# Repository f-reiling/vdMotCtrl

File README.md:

# vdMotCtrl
Controls up to 6 HmIP-VDMOT drives via I2C or UART interface. 

PCB uses ATmega168P as controller with L9110s as drivers. External interfaces are I2C and UART. Socket for ESP12 is also availble for wireless connection. 2 PCBs can be stacked, communication is planned via I2C then.

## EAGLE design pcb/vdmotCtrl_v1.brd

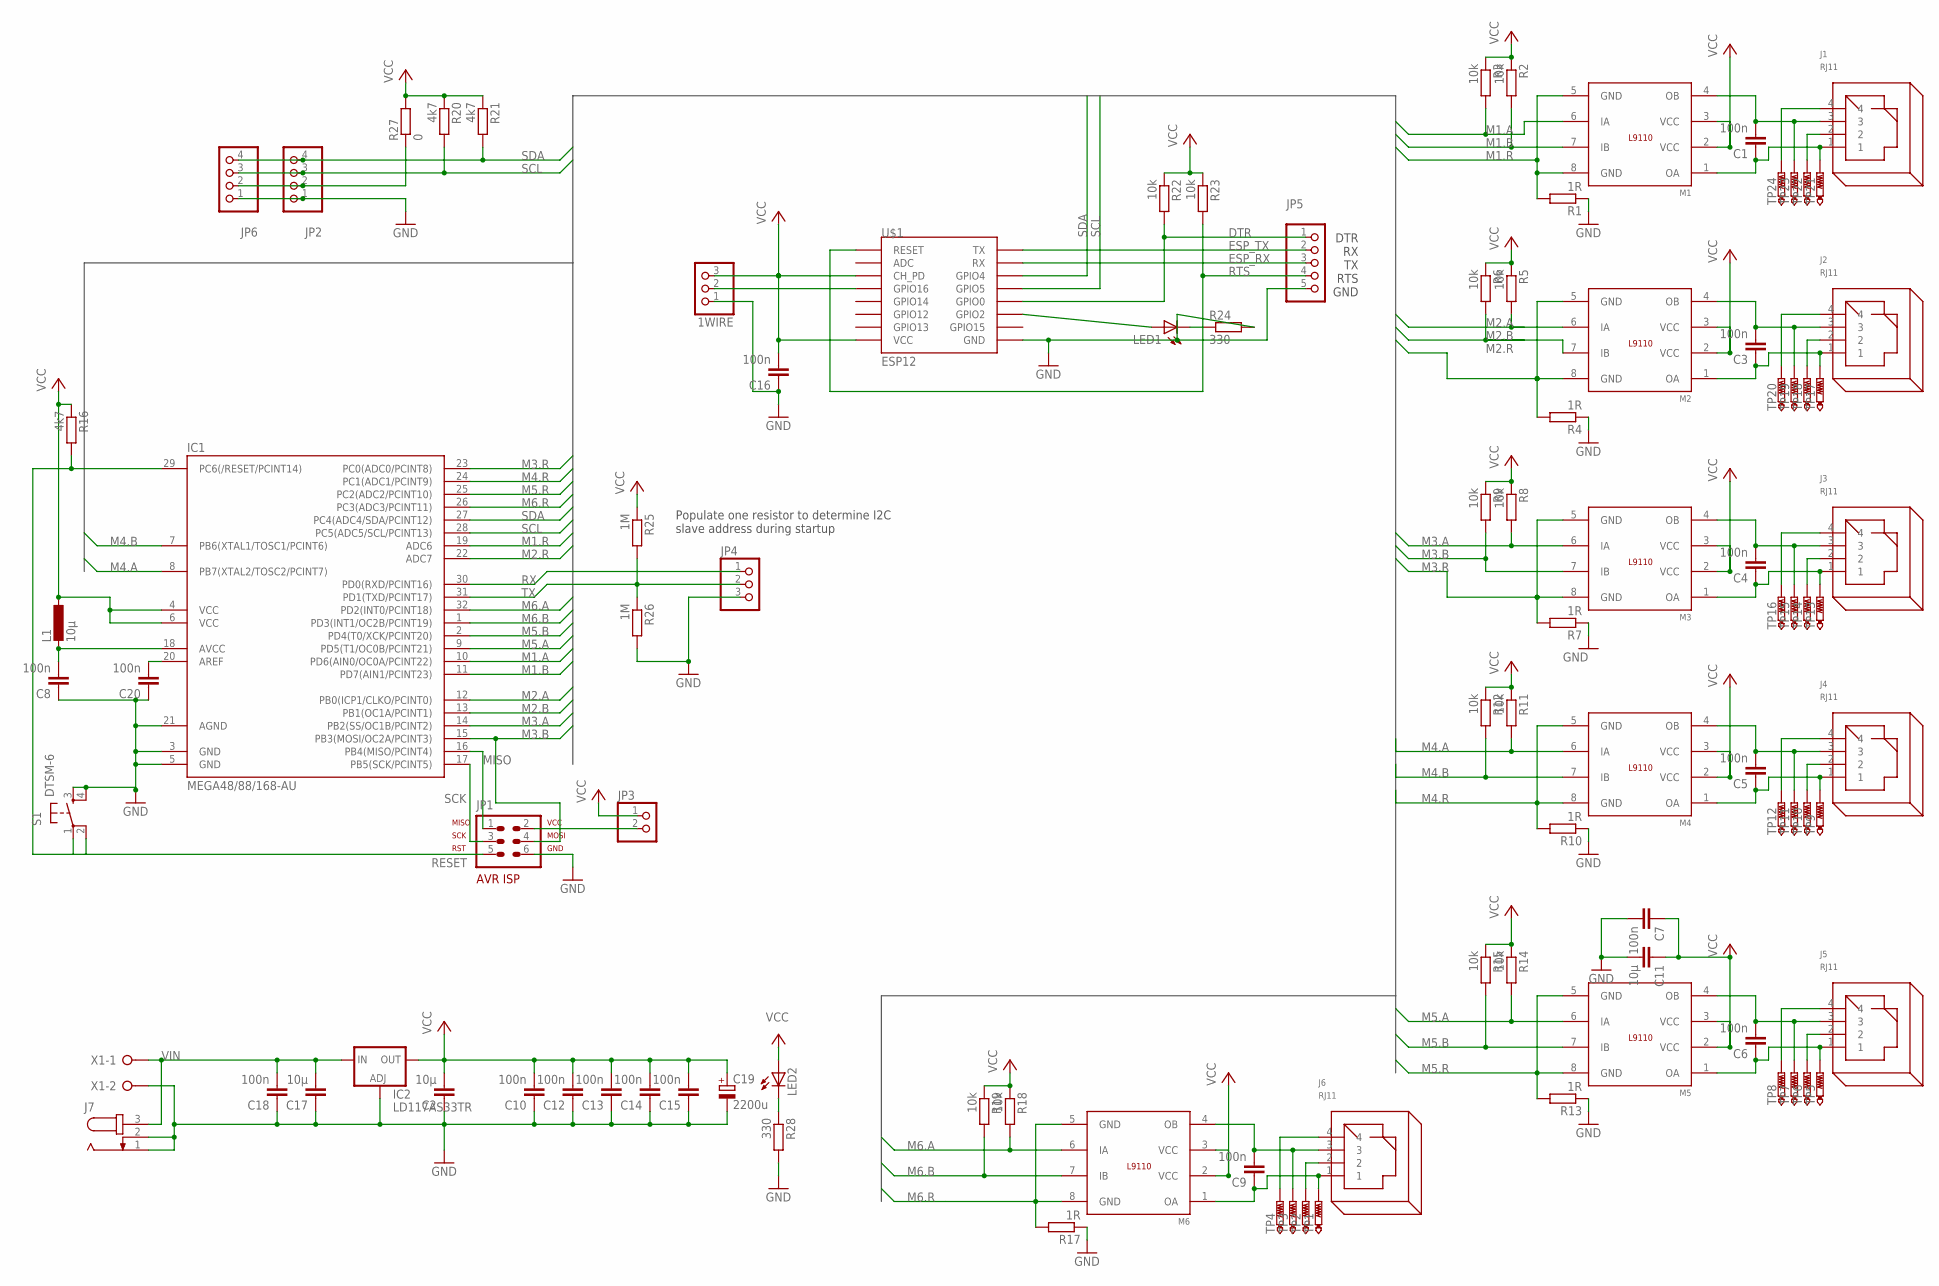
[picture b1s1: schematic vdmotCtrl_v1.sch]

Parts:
1WIRE: PINHD-1X3; 1X03
C1, C3, C4, C5, C6, C7, C8, C9, C10, C12, C13, C14, C15, C16, C18, C20: 100n; C0805
C2, C11, C17: 10µ; C0805
C19: 2200u; E5-10,5
IC1: MEGA48/88/168-AU; TQFP32-08
IC2: LD117AS33TR; SOT223
J1, J2, J3, J4, J5, J6: RJ11
J7: JACK-PLUG0; SPC4077
JP1: AVR-ISP-6VERT; AVR-ISP-6
JP2, JP6: PINHD-1X4; 1X04
JP3: PINHD-1X2; 1X02
JP4: PINHD-1X3; 1X03
JP5: PINHD-1X5; 1X05
L1: 10µ; 0204/7
LED1, LED2: RED; SML0805
M1, M2, M3, M4, M5, M6: L9110; SO8P
R1, R4, R7, R10, R13, R17: 1R; R0805
R2, R3, R5, R6, R8, R9, R11, R12, R14, R15, R18, R19, R22, R23: 10k; R0805
R16, R20, R21: 4k7; R0805
R24, R28: 330; R0805
R25, R26: 1M; R0805
R27: 0; M0805
S1: DTSM-6
TP1, TP2, TP3, TP4, TP5, TP6, TP7, TP8, TP9, TP10, TP11, TP12, TP13, TP14, TP15, TP16, TP17, TP18, TP19, TP20, TP21, TP22, TP23, TP24: PTR1TP15SQ; TP15SQ
U$1: ESP12
X1: W237-02P; W237-132

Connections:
DTR: JP5.1, R22.2, U$1.GPIO0
ESP_RX: JP5.3, U$1.RX
ESP_TX: JP5.2, U$1.TX
GND: 1WIRE.1, C2.1, C7.2, C8.1, C10.1, C11.2, C12.1, C13.1, C14.1, C15.1, C16.1, C17.1, C18.1, C19.-, C20.1, IC1.3 (GND), IC1.5 (GND), IC1.21 (AGND), IC2.1 (ADJ), J7.1, J7.2, JP1.6, JP2.1, JP4.3, JP5.5, JP6.1, R1.1, R4.1, R7.1, R10.1, R13.1, R17.1, R24.2, R26.2, R28.2, S1.3, S1.4, U$1.GND, X1.2
M1.A: IC1.10 (PD6(AIN0/OC0A/PCINT22)), M1.6 (IA), R3.2
M1.B: IC1.11 (PD7(AIN1/PCINT23)), M1.7 (IB), R2.2
M1.R: IC1.19 (ADC6), M1.5 (GND), M1.8 (GND), R1.2
M2.A: IC1.12 (PB0(ICP1/CLKO/PCINT0)), M2.6 (IA), R5.2
M2.B: IC1.13 (PB1(OC1A/PCINT1)), M2.7 (IB), R6.2
M2.R: IC1.22 (ADC7), M2.5 (GND), M2.8 (GND), R4.2
M3.A: IC1.14 (PB2(SS/OC1B/PCINT2)), M3.6 (IA), R8.2
M3.B: IC1.15 (PB3(MOSI/OC2A/PCINT3)), JP1.4, M3.7 (IB), R9.2
M3.R: IC1.23 (PC0(ADC0/PCINT8)), M3.5 (GND), M3.8 (GND), R7.2
M4.A: IC1.8 (PB7(XTAL2/TOSC2/PCINT7)), M4.6 (IA), R11.2
M4.B: IC1.7 (PB6(XTAL1/TOSC1/PCINT6)), M4.7 (IB), R12.2
M4.R: IC1.24 (PC1(ADC1/PCINT9)), M4.5 (GND), M4.8 (GND), R10.2
M5.A: IC1.9 (PD5(T1/OC0B/PCINT21)), M5.6 (IA), R14.2
M5.B: IC1.2 (PD4(T0/XCK/PCINT20)), M5.7 (IB), R15.2
M5.R: IC1.25 (PC2(ADC2/PCINT10)), M5.5 (GND), M5.8 (GND), R13.2
M6.A: IC1.32 (PD2(INT0/PCINT18)), M6.6 (IA), R18.2
M6.B: IC1.1 (PD3(INT1/OC2B/PCINT19)), M6.7 (IB), R19.2
M6.R: IC1.26 (PC3(ADC3/PCINT11)), M6.5 (GND), M6.8 (GND), R17.2
MISO: IC1.16 (PB4(MISO/PCINT4)), JP1.1
unnamed: C1.1, J1.1, M1.1 (OA), TP21.TP
unnamed: C1.2, J1.3, M1.4 (OB), TP23.TP
unnamed: C3.1, J2.1, M2.1 (OA), TP17.TP
unnamed: C3.2, J2.3, M2.4 (OB), TP19.TP
unnamed: C4.1, J3.1, M3.1 (OA), TP13.TP
unnamed: C4.2, J3.3, M3.4 (OB), TP15.TP
unnamed: C5.1, J4.1, M4.1 (OA), TP9.TP
unnamed: C5.2, J4.3, M4.4 (OB), TP11.TP
unnamed: C6.1, J5.1, M5.1 (OA), TP5.TP
unnamed: C6.2, J5.3, M5.4 (OB), TP7.TP
unnamed: C20.2, IC1.20 (AREF)
unnamed: C8.2, IC1.18 (AVCC), L1.2
unnamed: J6.2, TP2.TP
unnamed: LED1.A, U$1.GPIO2
unnamed: C9.1, J6.1, M6.1 (OA), TP1.TP
unnamed: C9.2, J6.3, M6.4 (OB), TP3.TP
unnamed: LED1.C, R24.1
unnamed: J6.4, TP4.TP
unnamed: J1.2, TP22.TP
unnamed: J1.4, TP24.TP
unnamed: JP1.2, JP3.2
unnamed: J2.2, TP18.TP
unnamed: J2.4, TP20.TP
unnamed: J3.4, TP16.TP
unnamed: J3.2, TP14.TP
unnamed: J4.4, TP12.TP
unnamed: J4.2, TP10.TP
unnamed: J5.4, TP8.TP
unnamed: J5.2, TP6.TP
unnamed: JP2.2, JP6.2, R27.1
unnamed: 1WIRE.2, U$1.GPIO16
unnamed: LED2.C, R28.1
RESET: IC1.29 (PC6(/RESET/PCINT14)), JP1.5, R16.2, S1.1, S1.2
RTS: JP5.4, R23.2, U$1.RESET
RX: IC1.30 (PD0(RXD/PCINT16)), JP4.1
SCK: IC1.17 (PB5(SCK/PCINT5)), JP1.3
SCL: IC1.28 (PC5(ADC5/SCL/PCINT13)), JP2.3, JP6.3, R20.2, U$1.GPIO5
SDA: IC1.27 (PC4(ADC4/SDA/PCINT12)), JP2.4, JP6.4, R21.2, U$1.GPIO4
TX: IC1.31 (PD1(TXD/PCINT17)), JP4.2, R25.2, R26.1
VCC: 1WIRE.3, C2.2, C7.1, C10.2, C11.1, C12.2, C13.2, C14.2, C15.2, C16.2, C19.+, IC1.4 (VCC), IC1.6 (VCC), IC2.4 (OUT), JP3.1, L1.1, LED2.A, M1.2 (VCC), M1.3 (VCC), M2.2 (VCC), M2.3 (VCC), M3.2 (VCC), M3.3 (VCC), M4.2 (VCC), M4.3 (VCC), M5.2 (VCC), M5.3 (VCC), M6.2 (VCC), M6.3 (VCC), R2.1, R3.1, R5.1, R6.1, R8.1, R9.1, R11.1, R12.1, R14.1, R15.1, R16.1, R18.1, R19.1, R20.1, R21.1, R22.1, R23.1, R25.1, R27.2, U$1.CH_PD, U$1.VCC
VIN: C17.2, C18.2, IC2.3 (IN), J7.3, X1.1

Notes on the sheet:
DTR RX TX RTS GND
Populate one resistor to determine I2C slave address during startup

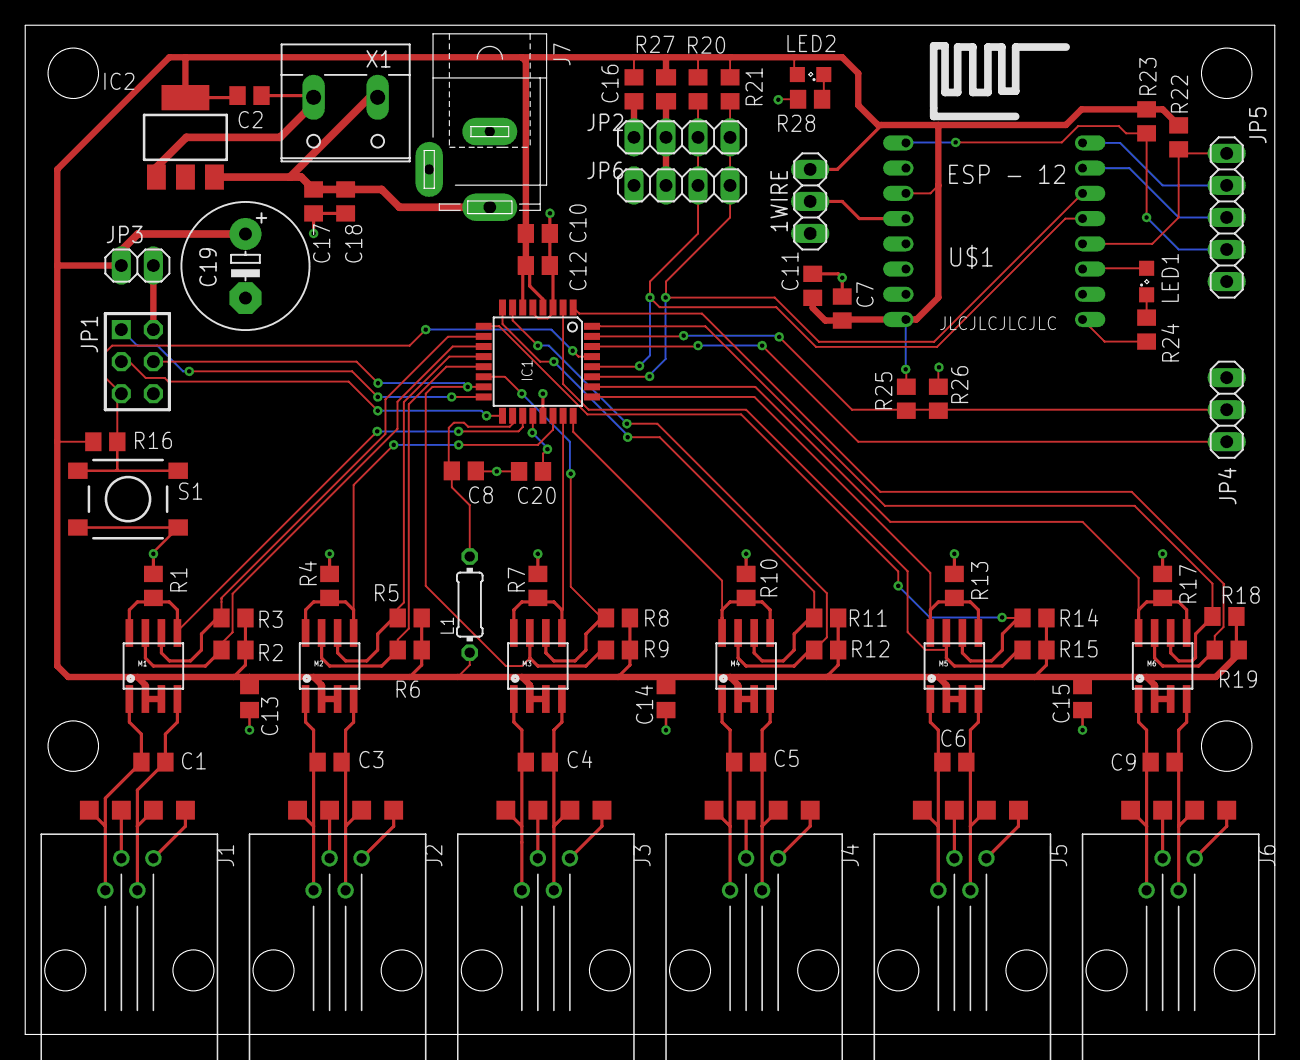
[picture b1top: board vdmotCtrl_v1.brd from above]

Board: 2 copper layers, 99.1 x 80.0 mm, 100 parts (0 on the bottom side), 64 nets.

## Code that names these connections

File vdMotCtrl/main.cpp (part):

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    
    
    // drives connected to PINA, PINB, ADCNum
    drives[0] = vdmot(0x36, 0x37, 6); // PD6, PD7, ADC6
    drives[1] = vdmot(0x10, 0x11, 7); // PB0, PB1, ADC7
    drives[2] = vdmot(0x12, 0x13, 0); // PB2, PB3, ADC0
    drives[3] = vdmot(0x16, 0x17, 1); // PB6, PB7, ADC1
    drives[4] = vdmot(0x35, 0x34, 2); // PD5, PD4, ADC2
    drives[5] = vdmot(0x32, 0x33, 3); // PD2, PD3, ADC3
    
    // TODO: read calibration values from EEP
    HWE::eepRead(0U, sizeof(nvmParam), (void*)&nvmParam );
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
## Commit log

2020-01-15 initial project setup
2020-02-02 added prototype PCB
2020-02-02 first running version. 2 drives. adaption working, movement working. some uart commands implemented for tests.
2020-02-02 added support for all 6 drives added task load monitoring in data visualizer code beautfying
2020-02-06 changed to correct target
2020-02-06 fixed I2C communication
2020-02-06 move drive only if in state IDLE
2020-02-06 added picture of prototype
2020-02-11 added command: move
2020-02-13 changed i2c command structure
2020-02-13 added command: move relative fixed I2C ST mode improved task load
2020-03-05 added support for EEP updated command handler
2020-05-01 added uart support for 6 drives. added nvm default values
